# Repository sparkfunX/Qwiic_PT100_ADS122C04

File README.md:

# Qwiic PT100 ADS122C04

The Qwiic PT100 is based on the TI ADS122C04 and allows you to measure temperature accurately from
100 Ohm Platinum Resistance Thermometers using 2, 3 or 4-wire connections

[Qwiic PT100 - ADS122C04 (SPX-16770)](https://www.sparkfun.com/products/16770)

The ADS122C04 is a precision 24-bit delta-sigma analog to digital converter. It can measure voltage very
accurately through two differential or four single-ended inputs. It has a flexible input multiplexer,
a low-noise programmable gain amplifier, two programmable current sources, a voltage reference
and an in-built precision temperature sensor. In summary, it contains everything you need to measure
temperature accurately from remote sensors.

The Qwiic PT100 is dedicated to reading the temperature of 100 Ohm Platinum Resistance Thermometers
using 2, 3 or 4-wire connections. Using a 3 or 4-wire connection allows the ADS122C04 to automatically
compensate for the cable resistance. The differential input provides noise rejection for industrial
applications.

The ADS122C04 features a 2-wire I2C-compatible interface. The chip address can be changed by
reconfiguring the two jumpers A0 and A1. Please see the schematic for further details.

## Repository Contents
- **/Hardware** - Eagle schematic and PCB design files
- **/Documents** - contains the TI datasheet and application reports
- **LICENSE.md** contains the licence information

## Library

- **[Arduino Library](https://github.com/sparkfun/SparkFun_ADS122C04_ADC_Arduino_Library)** - Library to support the ADS122C04

## Probe Disconnection

If you need to test if the PT100 probe has been connected correctly to the ADS122C04, you may find [this discussion](https://forum.sparkfun.com/viewtopic.php?p=231735#p231735) useful.

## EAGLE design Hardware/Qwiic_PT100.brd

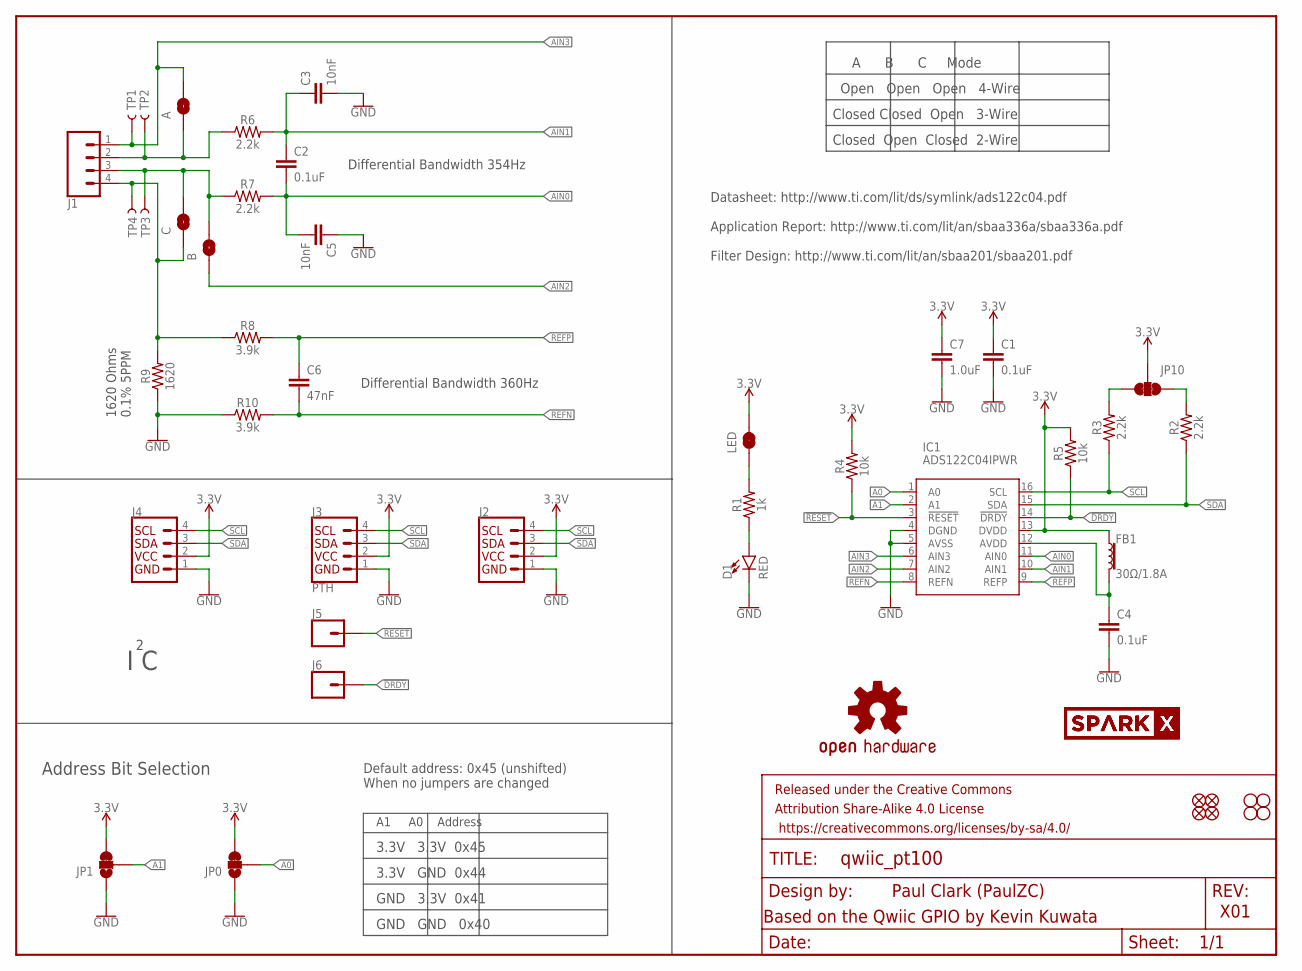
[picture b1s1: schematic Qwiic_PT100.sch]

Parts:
A: JUMPER-SMT_2_NO_SILK_ROUND; SMT-JUMPER_2_NO_SILK_ROUND
B: JUMPER-SMT_2_NO_SILK_ROUND; SMT-JUMPER_2_NO_SILK_ROUND
C: JUMPER-SMT_2_NO_SILK_ROUND; SMT-JUMPER_2_NO_SILK_ROUND
C1, C2, C4: 0.1uF; 0603
C3, C5: 10nF; 0603
C6: 47nF; 0603
C7: 1.0uF; 0603
D1: RED; LED-0603
FB1: 30Ω/1.8A; 0603
FD1, FD2: FIDUCIAL1X2; FIDUCIAL-1X2
FRAME1: FRAME-LETTER; CREATIVE_COMMONS
H1, H2: STAND-OFF
IC1: ADS122C04IPWR; SOP65P640X120-16N
J1: CONN_04LATCH; LATCHTERMINAL-5MM-4
J2, J4: QWIIC_RIGHT_ANGLE; JST04_1MM_RA
J3: PTH; 1X04_NO_SILK
J5, J6: CONN_01PTH_NO_SILK_YES_STOP; 1X01_NO_SILK
JP0, JP1: JUMPER-SMT_3_1-NC_TRACE_SILK; SMT-JUMPER_3_1-NC_TRACE_SILK
JP2, JP6: FIDUCIAL1X2; FIDUCIAL-1X2
JP3, JP4: STAND-OFF
JP10: JUMPER-SMT_3_2-NC_TRACE_SILK; SMT-JUMPER_3_2-NC_TRACE_SILK
LED: JUMPER-SMT_2_NC_TRACE_SILK; SMT-JUMPER_2_NC_TRACE_SILK
LOGO1: OSHW-LOGOMINI; OSHW-LOGO-MINI
R1: 1k; 0603
R2, R3, R6, R7: 2.2k; 0603
R4, R5: 10k; 0603
R8, R10: 3.9k; 0603
R9: 1620; 0603
TP1, TP2, TP3, TP4: TEST-POINTTP_15TH_THRU; TP_15TH
U$1, U$2: SPARKX-LOGO3; SPARKX-SMALL

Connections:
3.3V: C1.1, C7.1, FB1.1, IC1.13 (DVDD), J2.2, J3.2, J4.2, JP0.3, JP1.3, JP10.2, LED.2, R4.2, R5.2
!DRDY: IC1.14 (!DRDY), J6.1, R5.1
!RESET: IC1.3 (!RESET), J5.1, R4.1
A0: IC1.1 (A0), JP0.2
A1: IC1.2 (A1), JP1.2
AIN0: C2.2, C5.2, IC1.11 (AIN0), R7.2
AIN1: C2.1, C3.1, IC1.10 (AIN1), R6.2
AIN2: B.1, IC1.7 (AIN2)
AIN3: A.2, IC1.6 (AIN3), J1.1, TP1.P$1
GND: C1.2, C3.2, C4.2, C5.1, C7.2, D1.C, IC1.4 (DGND), IC1.5 (AVSS), J2.1, J3.1, J4.1, JP0.1, JP1.1, R9.1, R10.1
unnamed: A.1, J1.2, R6.1, TP2.P$1
unnamed: D1.A, R1.1
unnamed: LED.1, R1.2
unnamed: C4.1, FB1.2, IC1.12 (AVDD)
unnamed: B.2, C.2, J1.3, R7.1, TP3.P$1
unnamed: C.1, J1.4, R8.1, R9.2, TP4.P$1
REFN: C6.2, IC1.8 (REFN), R10.2
REFP: C6.1, IC1.9 (REFP), R8.2
SCL: IC1.16 (SCL), J2.4, J3.4, J4.4, R3.1
SCL_PU1: JP10.1, R2.2
SDA: IC1.15 (SDA), J2.3, J3.3, J4.3, R2.1
SDA_PU1: JP10.3, R3.2

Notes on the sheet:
Paul Clark (PaulZC)
X01
I C
Address Bit Selection
A1 A0 Address
3.3V 3.3V 0x45
3.3V GND 0x44
GND 3.3V 0x41
GND GND 0x40
Default address: 0x45 (unshifted) When no jumpers are changed
Based on the Qwiic GPIO by Kevin Kuwata
A B C Mode
Open Open Open 4-Wire
Closed Closed Open 3-Wire
Closed Open Closed 2-Wire
Datasheet: http://www.ti.com/lit/ds/symlink/ads122c04.pdf Application Report: http://www.ti.com/lit/an/sbaa336a/sbaa336a.pdf Filter Design: http://www.ti.com/lit/an/sbaa201/sbaa201.pdf
1620 Ohms 0.1% 5PPM
Differential Bandwidth 354Hz
Differential Bandwidth 360Hz

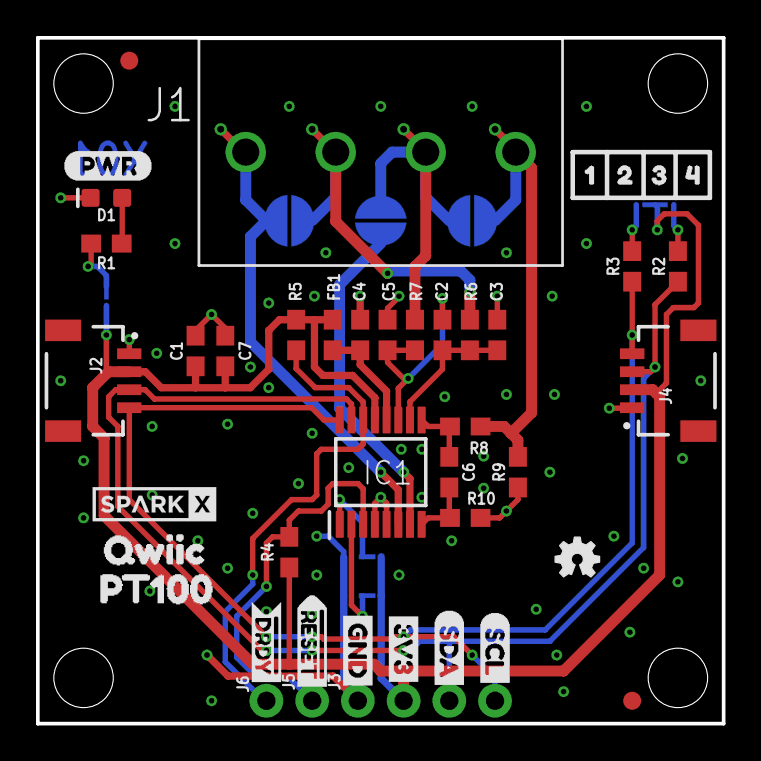
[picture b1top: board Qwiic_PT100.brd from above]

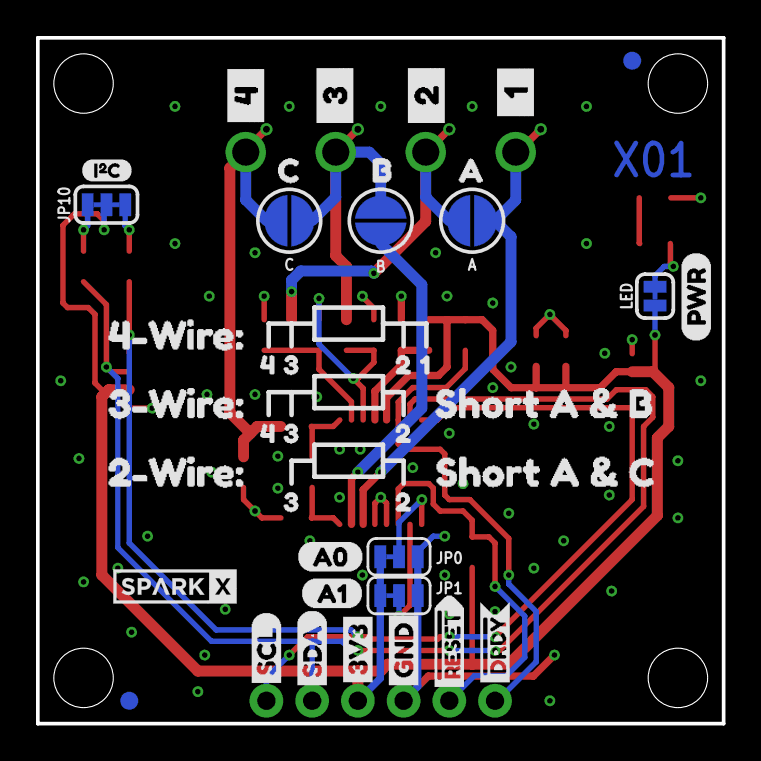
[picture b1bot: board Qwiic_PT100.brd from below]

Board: 2 copper layers, 38.1 x 38.1 mm, 93 parts (41 on the bottom side), 22 nets.

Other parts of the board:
U$3, U$26: 3V33
U$4: _1_0
U$5: A11
U$6: _2_0
U$7, U$25: GND4
U$8: PT1000
U$9: SCL6
U$10: SDA5
U$11: A00
U$12: _3_0
U$13: _4_0
U$14, U$15: #DRDY0
U$16, U$17: #RESET0
U$18: A0
U$19: B0
U$20: I_SUPER2_C-()-03
U$21, U$30, U$44: 40
U$22: C0
U$23: SCL0
U$24: SDA1
U$27, U$34, U$38, U$47: 31
U$28, U$33, U$37, U$46: 20
U$29, U$35: 15
U$31: 2#WIRE#0
U$32: QWIIC1
U$36: 3#WIRE#0
U$39, U$40: PWR0
U$41: 4#WIRE#0
U$42: SHORT_A_#_B0
U$43: SHORT_A_#_C0

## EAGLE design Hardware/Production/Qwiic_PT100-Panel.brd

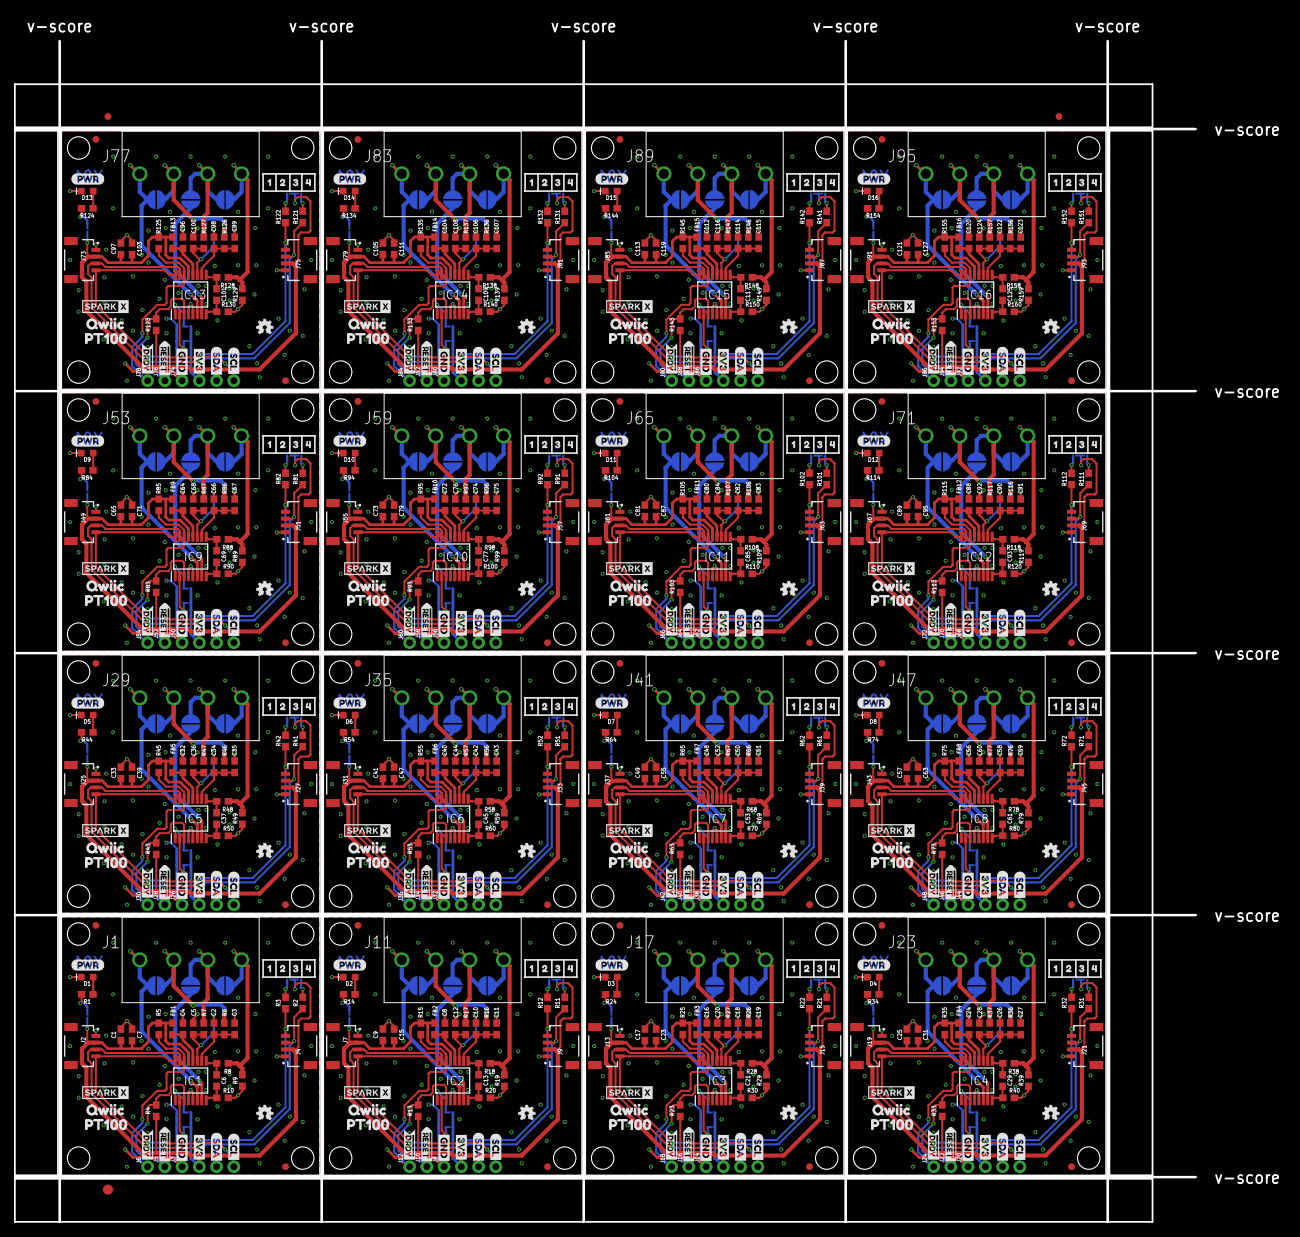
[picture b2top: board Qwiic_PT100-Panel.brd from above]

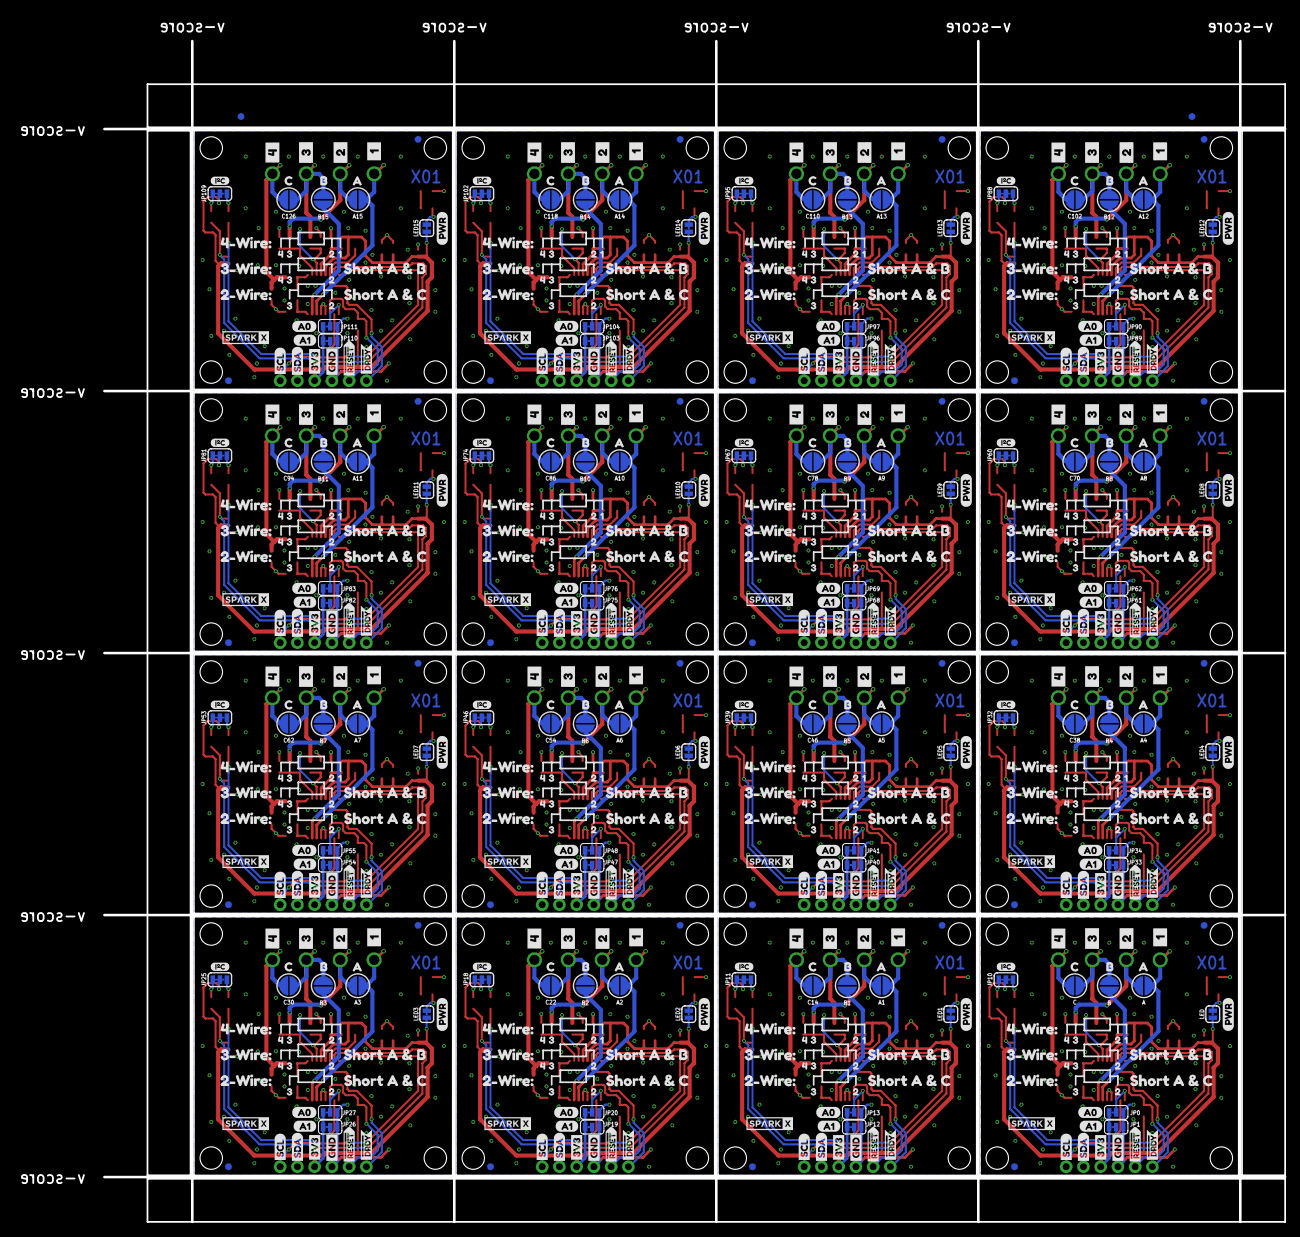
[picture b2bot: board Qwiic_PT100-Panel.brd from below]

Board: 2 copper layers, 174.0 x 174.0 mm, 1477 parts (658 on the bottom side), 352 nets.

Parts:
A, A1, A2, A3, A4, A5, A6, A7, A8, A9, A10, A11, A12, A13, A14, A15: JUMPER-SMT_2_NO_SILK_ROUND; SMT-JUMPER_2_NO_SILK_ROUND
B, B1, B2, B3, B4, B5, B6, B7, B8, B9, B10, B11, B12, B13, B14, B15: JUMPER-SMT_2_NO_SILK_ROUND; SMT-JUMPER_2_NO_SILK_ROUND
C, C14, C22, C30, C38, C46, C54, C62, C70, C78, C86, C94, C102, C110, C118, C126: JUMPER-SMT_2_NO_SILK_ROUND; SMT-JUMPER_2_NO_SILK_ROUND
C1, C2, C4, C8, C9, C10, C16, C17, C18, C24, C25, C26, C32, C33, C34, C40, C41, C42, C48, C49, C50, C56, C57, C58, C64, C65, C66, C72, C73, C74, C80, C81, C82, C88, C89, C90, C96, C97, C98, C104, C105, C106, C112, C113, C114, C120, C121, C122: 0.1uF; 0603
C3, C5, C11, C12, C19, C20, C27, C28, C35, C36, C43, C44, C51, C52, C59, C60, C67, C68, C75, C76, C83, C84, C91, C92, C99, C100, C107, C108, C115, C116, C123, C124: 10nF; 0603
C6, C13, C21, C29, C37, C45, C53, C61, C69, C77, C85, C93, C101, C109, C117, C125: 47nF; 0603
C7, C15, C23, C31, C39, C47, C55, C63, C71, C79, C87, C95, C103, C111, C119, C127: 1.0uF; 0603
D1, D2, D3, D4, D5, D6, D7, D8, D9, D10, D11, D12, D13, D14, D15, D16: RED; LED-0603
E$1, E$2, E$3, E$4: FIDUCIAL-1X2
E$5: FIDUCIAL-1.5X3
FB1, FB2, FB3, FB4, FB5, FB6, FB7, FB8, FB9, FB10, FB11, FB12, FB13, FB14, FB15, FB16: 30Ω/1.8A; 0603
FD1, FD2, FD3, FD4, FD5, FD6, FD7, FD8, FD9, FD10, FD11, FD12, FD13, FD14, FD15, FD16, FD17, FD18, FD19, FD20, FD21, FD22, FD23, FD24, FD25, FD26, FD27, FD28, FD29, FD30, FD31, FD32: FIDUCIAL1X2; FIDUCIAL-1X2
H1, H2, H3, H4, H5, H6, H7, H8, H9, H10, H11, H12, H13, H14, H15, H16, H17, H18, H19, H20, H21, H22, H23, H24, H25, H26, H27, H28, H29, H30, H31, H32: STAND-OFF
IC1, IC2, IC3, IC4, IC5, IC6, IC7, IC8, IC9, IC10, IC11, IC12, IC13, IC14, IC15, IC16: ADS122C04IPWR; SOP65P640X120-16N
J1, J11, J17, J23, J29, J35, J41, J47, J53, J59, J65, J71, J77, J83, J89, J95: LATCHTERMINAL-5MM-4
J2, J4, J7, J9, J13, J15, J19, J21, J25, J27, J31, J33, J37, J39, J43, J45, J49, J51, J55, J57, J61, J63, J67, J69, J73, J75, J79, J81, J85, J87, J91, J93: QWIIC_RIGHT_ANGLE; JST04_1MM_RA
J3, J8, J14, J20, J26, J32, J38, J44, J50, J56, J62, J68, J74, J80, J86, J92: PTH; 1X04_NO_SILK
J5, J6, J10, J12, J16, J18, J22, J24, J28, J30, J34, J36, J40, J42, J46, J48, J52, J54, J58, J60, J64, J66, J70, J72, J76, J78, J82, J84, J88, J90, J94, J96: 1X01_NO_SILK
JP0, JP1, JP12, JP13, JP19, JP20, JP26, JP27, JP33, JP34, JP40, JP41, JP47, JP48, JP54, JP55, JP61, JP62, JP68, JP69, JP75, JP76, JP82, JP83, JP89, JP90, JP96, JP97, JP103, JP104, JP110, JP111: JUMPER-SMT_3_1-NC_TRACE_SILK; SMT-JUMPER_3_1-NC_TRACE_SILK
JP2, JP6, JP8, JP9, JP16, JP17, JP23, JP24, JP30, JP31, JP37, JP38, JP44, JP45, JP51, JP52, JP58, JP59, JP65, JP66, JP72, JP73, JP79, JP80, JP86, JP87, JP93, JP94, JP100, JP101, JP107, JP108: FIDUCIAL1X2; FIDUCIAL-1X2
JP3, JP4, JP5, JP7, JP14, JP15, JP21, JP22, JP28, JP29, JP35, JP36, JP42, JP43, JP49, JP50, JP56, JP57, JP63, JP64, JP70, JP71, JP77, JP78, JP84, JP85, JP91, JP92, JP98, JP99, JP105, JP106: STAND-OFF
JP10, JP11, JP18, JP25, JP32, JP39, JP46, JP53, JP60, JP67, JP74, JP81, JP88, JP95, JP102, JP109: JUMPER-SMT_3_2-NC_TRACE_SILK; SMT-JUMPER_3_2-NC_TRACE_SILK
LED, LED1, LED2, LED3, LED4, LED5, LED6, LED7, LED8, LED9, LED10, LED11, LED12, LED13, LED14, LED15: JUMPER-SMT_2_NC_TRACE_SILK; SMT-JUMPER_2_NC_TRACE_SILK
LOGO1, LOGO2, LOGO3, LOGO4, LOGO5, LOGO6, LOGO7, LOGO8, LOGO9, LOGO10, LOGO11, LOGO12, LOGO13, LOGO14, LOGO15, LOGO16: OSHW-LOGOMINI; OSHW-LOGO-MINI
R1, R14, R24, R34, R44, R54, R64, R74, R84, R94, R104, R114, R124, R134, R144, R154: 1k; 0603
R2, R3, R6, R7, R11, R12, R16, R17, R21, R22, R26, R27, R31, R32, R36, R37, R41, R42, R46, R47, R51, R52, R56, R57, R61, R62, R66, R67, R71, R72, R76, R77, R81, R82, R86, R87, R91, R92, R96, R97, R101, R102, R106, R107, R111, R112, R116, R117, R121, R122, R126, R127, R131, R132, R136, R137, R141, R142, R146, R147, R151, R152, R156, R157: 2.2k; 0603
R4, R5, R13, R15, R23, R25, R33, R35, R43, R45, R53, R55, R63, R65, R73, R75, R83, R85, R93, R95, R103, R105, R113, R115, R123, R125, R133, R135, R143, R145, R153, R155: 10k; 0603
R8, R10, R18, R20, R28, R30, R38, R40, R48, R50, R58, R60, R68, R70, R78, R80, R88, R90, R98, R100, R108, R110, R118, R120, R128, R130, R138, R140, R148, R150, R158, R160: 3.9k; 0603
R9, R19, R29, R39, R49, R59, R69, R79, R89, R99, R109, R119, R129, R139, R149, R159: 1620; 0603
TP1, TP2, TP3, TP4, TP5, TP6, TP7, TP8, TP9, TP10, TP11, TP12, TP13, TP14, TP15, TP16, TP17, TP18, TP19, TP20, TP21, TP22, TP23, TP24, TP25, TP26, TP27, TP28, TP29, TP30, TP31, TP32, TP33, TP34, TP35, TP36, TP37, TP38, TP39, TP40, TP41, TP42, TP43, TP44, TP45, TP46, TP47, TP48, TP49, TP50, TP51, TP52, TP53, TP54, TP55, TP56, TP57, TP58, TP59, TP60, TP61, TP62, TP63, TP64: TEST-POINTTP_15TH_THRU; TP_15TH
U$1, U$2, U$45, U$48, U$93, U$94, U$139, U$140, U$185, U$186, U$231, U$232, U$277, U$278, U$323, U$324, U$369, U$370, U$415, U$416, U$461, U$462, U$507, U$508, U$553, U$554, U$599, U$600, U$645, U$646, U$691, U$692: SPARKX-LOGO3; SPARKX-SMALL
U$3, U$26, U$49, U$59, U$95, U$105, U$141, U$151, U$187, U$197, U$233, U$243, U$279, U$289, U$325, U$335, U$371, U$381, U$417, U$427, U$463, U$473, U$509, U$519, U$555, U$565, U$601, U$611, U$647, U$657, U$693, U$703: 3V33
U$4, U$66, U$112, U$158, U$204, U$250, U$296, U$342, U$388, U$434, U$480, U$526, U$572, U$618, U$664, U$710: _1_0
U$5, U$50, U$96, U$142, U$188, U$234, U$280, U$326, U$372, U$418, U$464, U$510, U$556, U$602, U$648, U$694: A11
U$6, U$67, U$113, U$159, U$205, U$251, U$297, U$343, U$389, U$435, U$481, U$527, U$573, U$619, U$665, U$711: _2_0
U$7, U$25, U$51, U$58, U$97, U$104, U$143, U$150, U$189, U$196, U$235, U$242, U$281, U$288, U$327, U$334, U$373, U$380, U$419, U$426, U$465, U$472, U$511, U$518, U$557, U$564, U$603, U$610, U$649, U$656, U$695, U$702: GND4
U$8, U$78, U$124, U$170, U$216, U$262, U$308, U$354, U$400, U$446, U$492, U$538, U$584, U$630, U$676, U$722: PT1000
U$9, U$52, U$98, U$144, U$190, U$236, U$282, U$328, U$374, U$420, U$466, U$512, U$558, U$604, U$650, U$696: SCL6
U$10, U$53, U$99, U$145, U$191, U$237, U$283, U$329, U$375, U$421, U$467, U$513, U$559, U$605, U$651, U$697: SDA5
U$11, U$54, U$100, U$146, U$192, U$238, U$284, U$330, U$376, U$422, U$468, U$514, U$560, U$606, U$652, U$698: A00
U$12, U$68, U$114, U$160, U$206, U$252, U$298, U$344, U$390, U$436, U$482, U$528, U$574, U$620, U$666, U$712: _3_0
U$13, U$69, U$115, U$161, U$207, U$253, U$299, U$345, U$391, U$437, U$483, U$529, U$575, U$621, U$667, U$713: _4_0
U$14, U$15, U$70, U$71, U$116, U$117, U$162, U$163, U$208, U$209, U$254, U$255, U$300, U$301, U$346, U$347, U$392, U$393, U$438, U$439, U$484, U$485, U$530, U$531, U$576, U$577, U$622, U$623, U$668, U$669, U$714, U$715: #DRDY0
U$16, U$17, U$72, U$73, U$118, U$119, U$164, U$165, U$210, U$211, U$256, U$257, U$302, U$303, U$348, U$349, U$394, U$395, U$440, U$441, U$486, U$487, U$532, U$533, U$578, U$579, U$624, U$625, U$670, U$671, U$716, U$717: #RESET0
U$18, U$74, U$120, U$166, U$212, U$258, U$304, U$350, U$396, U$442, U$488, U$534, U$580, U$626, U$672, U$718: A0
U$19, U$75, U$121, U$167, U$213, U$259, U$305, U$351, U$397, U$443, U$489, U$535, U$581, U$627, U$673, U$719: B0
U$20, U$55, U$101, U$147, U$193, U$239, U$285, U$331, U$377, U$423, U$469, U$515, U$561, U$607, U$653, U$699: I_SUPER2_C-()-03
U$21, U$30, U$44, U$77, U$86, U$89, U$123, U$132, U$135, U$169, U$178, U$181, U$215, U$224, U$227, U$261, U$270, U$273, U$307, U$316, U$319, U$353, U$362, U$365, U$399, U$408, U$411, U$445, U$454, U$457, U$491, U$500, U$503, U$537, U$546, U$549, U$583, U$592, U$595, U$629, U$638, U$641, U$675, U$684, U$687, U$721, U$730, U$733: 40
U$22, U$76, U$122, U$168, U$214, U$260, U$306, U$352, U$398, U$444, U$490, U$536, U$582, U$628, U$674, U$720: C0
U$23, U$56, U$102, U$148, U$194, U$240, U$286, U$332, U$378, U$424, U$470, U$516, U$562, U$608, U$654, U$700: SCL0
U$24, U$57, U$103, U$149, U$195, U$241, U$287, U$333, U$379, U$425, U$471, U$517, U$563, U$609, U$655, U$701: SDA1
U$27, U$34, U$38, U$47, U$63, U$85, U$88, U$90, U$109, U$131, U$134, U$136, U$155, U$177, U$180, U$182, U$201, U$223, U$226, U$228, U$247, U$269, U$272, U$274, U$293, U$315, U$318, U$320, U$339, U$361, U$364, U$366, U$385, U$407, U$410, U$412, U$431, U$453, U$456, U$458, U$477, U$499, U$502, U$504, U$523, U$545, U$548, U$550, U$569, U$591, U$594, U$596, U$615, U$637, U$640, U$642, U$661, U$683, U$686, U$688, U$707, U$729, U$732, U$734: 31
U$28, U$33, U$37, U$46, U$62, U$84, U$87, U$91, U$108, U$130, U$133, U$137, U$154, U$176, U$179, U$183, U$200, U$222, U$225, U$229, U$246, U$268, U$271, U$275, U$292, U$314, U$317, U$321, U$338, U$360, U$363, U$367, U$384, U$406, U$409, U$413, U$430, U$452, U$455, U$459, U$476, U$498, U$501, U$505, U$522, U$544, U$547, U$551, U$568, U$590, U$593, U$597, U$614, U$636, U$639, U$643, U$660, U$682, U$685, U$689, U$706, U$728, U$731, U$735: 20
U$29, U$35, U$61, U$92, U$107, U$138, U$153, U$184, U$199, U$230, U$245, U$276, U$291, U$322, U$337, U$368, U$383, U$414, U$429, U$460, U$475, U$506, U$521, U$552, U$567, U$598, U$613, U$644, U$659, U$690, U$705, U$736: 15
U$31, U$79, U$125, U$171, U$217, U$263, U$309, U$355, U$401, U$447, U$493, U$539, U$585, U$631, U$677, U$723: 2#WIRE#0
U$32, U$60, U$106, U$152, U$198, U$244, U$290, U$336, U$382, U$428, U$474, U$520, U$566, U$612, U$658, U$704: QWIIC1
U$36, U$80, U$126, U$172, U$218, U$264, U$310, U$356, U$402, U$448, U$494, U$540, U$586, U$632, U$678, U$724: 3#WIRE#0
U$39, U$40, U$64, U$65, U$110, U$111, U$156, U$157, U$202, U$203, U$248, U$249, U$294, U$295, U$340, U$341, U$386, U$387, U$432, U$433, U$478, U$479, U$524, U$525, U$570, U$571, U$616, U$617, U$662, U$663, U$708, U$709: PWR0
U$41, U$81, U$127, U$173, U$219, U$265, U$311, U$357, U$403, U$449, U$495, U$541, U$587, U$633, U$679, U$725: 4#WIRE#0
U$42, U$82, U$128, U$174, U$220, U$266, U$312, U$358, U$404, U$450, U$496, U$542, U$588, U$634, U$680, U$726: SHORT_A_#_B0
U$43, U$83, U$129, U$175, U$221, U$267, U$313, U$359, U$405, U$451, U$497, U$543, U$589, U$635, U$681, U$727: SHORT_A_#_C0

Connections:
3.3V: C1.1, C7.1, FB1.1, IC1.13, J2.2, J3.2, J4.2, JP0.3, JP1.3, JP10.2, LED.2, R4.2, R5.2
3.3V1: C9.1, C15.1, FB2.1, IC2.13, J7.2, J8.2, J9.2, JP11.2, JP12.3, JP13.3, LED1.2, R13.2, R15.2
3.3V2: C17.1, C23.1, FB3.1, IC3.13, J13.2, J14.2, J15.2, JP18.2, JP19.3, JP20.3, LED2.2, R23.2, R25.2
3.3V3: C25.1, C31.1, FB4.1, IC4.13, J19.2, J20.2, J21.2, JP25.2, JP26.3, JP27.3, LED3.2, R33.2, R35.2
3.3V4: C33.1, C39.1, FB5.1, IC5.13, J25.2, J26.2, J27.2, JP32.2, JP33.3, JP34.3, LED4.2, R43.2, R45.2
3.3V5: C41.1, C47.1, FB6.1, IC6.13, J31.2, J32.2, J33.2, JP39.2, JP40.3, JP41.3, LED5.2, R53.2, R55.2
3.3V6: C49.1, C55.1, FB7.1, IC7.13, J37.2, J38.2, J39.2, JP46.2, JP47.3, JP48.3, LED6.2, R63.2, R65.2
3.3V7: C57.1, C63.1, FB8.1, IC8.13, J43.2, J44.2, J45.2, JP53.2, JP54.3, JP55.3, LED7.2, R73.2, R75.2
3.3V8: C65.1, C71.1, FB9.1, IC9.13, J49.2, J50.2, J51.2, JP60.2, JP61.3, JP62.3, LED8.2, R83.2, R85.2
3.3V9: C73.1, C79.1, FB10.1, IC10.13, J55.2, J56.2, J57.2, JP67.2, JP68.3, JP69.3, LED9.2, R93.2, R95.2
3.3V10: C81.1, C87.1, FB11.1, IC11.13, J61.2, J62.2, J63.2, JP74.2, JP75.3, JP76.3, LED10.2, R103.2, R105.2
3.3V11: C89.1, C95.1, FB12.1, IC12.13, J67.2, J68.2, J69.2, JP81.2, JP82.3, JP83.3, LED11.2, R113.2, R115.2
3.3V12: C97.1, C103.1, FB13.1, IC13.13, J73.2, J74.2, J75.2, JP88.2, JP89.3, JP90.3, LED12.2, R123.2, R125.2
3.3V13: C105.1, C111.1, FB14.1, IC14.13, J79.2, J80.2, J81.2, JP95.2, JP96.3, JP97.3, LED13.2, R133.2, R135.2
3.3V14: C113.1, C119.1, FB15.1, IC15.13, J85.2, J86.2, J87.2, JP102.2, JP103.3, JP104.3, LED14.2, R143.2, R145.2
3.3V15: C121.1, C127.1, FB16.1, IC16.13, J91.2, J92.2, J93.2, JP109.2, JP110.3, JP111.3, LED15.2, R153.2, R155.2
!DRDY: IC1.14, J6.1, R5.1
!DRDY1: IC2.14, J12.1, R15.1
!DRDY2: IC3.14, J18.1, R25.1
!DRDY3: IC4.14, J24.1, R35.1
!DRDY4: IC5.14, J30.1, R45.1
!DRDY5: IC6.14, J36.1, R55.1
!DRDY6: IC7.14, J42.1, R65.1
!DRDY7: IC8.14, J48.1, R75.1
!DRDY8: IC9.14, J54.1, R85.1
!DRDY9: IC10.14, J60.1, R95.1
!DRDY10: IC11.14, J66.1, R105.1
!DRDY11: IC12.14, J72.1, R115.1
!DRDY12: IC13.14, J78.1, R125.1
!DRDY13: IC14.14, J84.1, R135.1
!DRDY14: IC15.14, J90.1, R145.1
!DRDY15: IC16.14, J96.1, R155.1
!RESET: IC1.3, J5.1, R4.1
!RESET1: IC2.3, J10.1, R13.1
!RESET2: IC3.3, J16.1, R23.1
!RESET3: IC4.3, J22.1, R33.1
!RESET4: IC5.3, J28.1, R43.1
!RESET5: IC6.3, J34.1, R53.1
!RESET6: IC7.3, J40.1, R63.1
!RESET7: IC8.3, J46.1, R73.1
!RESET8: IC9.3, J52.1, R83.1
!RESET9: IC10.3, J58.1, R93.1
!RESET10: IC11.3, J64.1, R103.1
!RESET11: IC12.3, J70.1, R113.1
!RESET12: IC13.3, J76.1, R123.1
!RESET13: IC14.3, J82.1, R133.1
!RESET14: IC15.3, J88.1, R143.1
!RESET15: IC16.3, J94.1, R153.1
A0: IC1.1, JP0.2
A1: IC1.2, JP1.2
A2: IC2.1, JP13.2
A3: IC2.2, JP12.2
A4: IC3.1, JP20.2
A5: IC3.2, JP19.2
A6: IC4.1, JP27.2
A7: IC4.2, JP26.2
A8: IC5.1, JP34.2
A9: IC5.2, JP33.2
A10: IC6.1, JP41.2
A11: IC6.2, JP40.2
A12: IC7.1, JP48.2
A13: IC7.2, JP47.2
A14: IC8.1, JP55.2
A15: IC8.2, JP54.2
A16: IC9.1, JP62.2
A17: IC9.2, JP61.2
A18: IC10.1, JP69.2
A19: IC10.2, JP68.2
A20: IC11.1, JP76.2
A21: IC11.2, JP75.2
A22: IC12.1, JP83.2
A23: IC12.2, JP82.2
A24: IC13.1, JP90.2
A25: IC13.2, JP89.2
A26: IC14.1, JP97.2
A27: IC14.2, JP96.2
A28: IC15.1, JP104.2
A29: IC15.2, JP103.2
A30: IC16.1, JP111.2
A31: IC16.2, JP110.2
AIN0: C2.2, C5.2, IC1.11, R7.2
AIN1: C2.1, C3.1, IC1.10, R6.2
AIN2: B.1, IC1.7
AIN3: A.2, IC1.6, J1.1, TP1.P$1
AIN4: C10.1, C11.1, IC2.10, R16.2
AIN5: A1.2, IC2.6, J11.1, TP5.P$1
AIN6: B1.1, IC2.7
AIN7: C10.2, C12.2, IC2.11, R17.2
AIN8: C18.1, C19.1, IC3.10, R26.2
AIN9: A2.2, IC3.6, J17.1, TP9.P$1
AIN10: B2.1, IC3.7
AIN11: C18.2, C20.2, IC3.11, R27.2
AIN12: C26.1, C27.1, IC4.10, R36.2
AIN13: A3.2, IC4.6, J23.1, TP13.P$1
AIN14: B3.1, IC4.7
AIN15: C26.2, C28.2, IC4.11, R37.2
AIN16: C34.1, C35.1, IC5.10, R46.2
AIN17: A4.2, IC5.6, J29.1, TP17.P$1
AIN18: B4.1, IC5.7
AIN19: C34.2, C36.2, IC5.11, R47.2
AIN20: C42.1, C43.1, IC6.10, R56.2
AIN21: A5.2, IC6.6, J35.1, TP21.P$1
AIN22: B5.1, IC6.7
AIN23: C42.2, C44.2, IC6.11, R57.2
AIN24: C50.1, C51.1, IC7.10, R66.2
AIN25: A6.2, IC7.6, J41.1, TP25.P$1
AIN26: B6.1, IC7.7
AIN27: C50.2, C52.2, IC7.11, R67.2
AIN28: C58.1, C59.1, IC8.10, R76.2
AIN29: A7.2, IC8.6, J47.1, TP29.P$1
AIN30: B7.1, IC8.7
AIN31: C58.2, C60.2, IC8.11, R77.2
AIN32: C66.1, C67.1, IC9.10, R86.2
AIN33: A8.2, IC9.6, J53.1, TP33.P$1
AIN34: B8.1, IC9.7
AIN35: C66.2, C68.2, IC9.11, R87.2
AIN36: C74.1, C75.1, IC10.10, R96.2
AIN37: A9.2, IC10.6, J59.1, TP37.P$1
AIN38: B9.1, IC10.7
AIN39: C74.2, C76.2, IC10.11, R97.2
AIN40: C82.1, C83.1, IC11.10, R106.2
AIN41: A10.2, IC11.6, J65.1, TP41.P$1
AIN42: B10.1, IC11.7
AIN43: C82.2, C84.2, IC11.11, R107.2
AIN44: C90.1, C91.1, IC12.10, R116.2
AIN45: A11.2, IC12.6, J71.1, TP45.P$1
AIN46: B11.1, IC12.7
AIN47: C90.2, C92.2, IC12.11, R117.2
AIN48: C98.1, C99.1, IC13.10, R126.2
AIN49: A12.2, IC13.6, J77.1, TP49.P$1
AIN50: B12.1, IC13.7
AIN51: C98.2, C100.2, IC13.11, R127.2
AIN52: C106.1, C107.1, IC14.10, R136.2
AIN53: A13.2, IC14.6, J83.1, TP53.P$1
AIN54: B13.1, IC14.7
AIN55: C106.2, C108.2, IC14.11, R137.2
AIN56: C114.1, C115.1, IC15.10, R146.2
AIN57: A14.2, IC15.6, J89.1, TP57.P$1
AIN58: B14.1, IC15.7
AIN59: C114.2, C116.2, IC15.11, R147.2
AIN60: C122.1, C123.1, IC16.10, R156.2
AIN61: A15.2, IC16.6, J95.1, TP61.P$1
AIN62: B15.1, IC16.7
AIN63: C122.2, C124.2, IC16.11, R157.2
GND: C1.2, C3.2, C4.2, C5.1, C7.2, D1.C, IC1.4, IC1.5, J2.1, J3.1, J4.1, JP0.1, JP1.1, R9.1, R10.1
GND1: C8.2, C9.2, C11.2, C12.1, C15.2, D2.C, IC2.4, IC2.5, J7.1, J8.1, J9.1, JP12.1, JP13.1, R19.1, R20.1
GND2: C16.2, C17.2, C19.2, C20.1, C23.2, D3.C, IC3.4, IC3.5, J13.1, J14.1, J15.1, JP19.1, JP20.1, R29.1, R30.1
GND3: C24.2, C25.2, C27.2, C28.1, C31.2, D4.C, IC4.4, IC4.5, J19.1, J20.1, J21.1, JP26.1, JP27.1, R39.1, R40.1
GND4: C32.2, C33.2, C35.2, C36.1, C39.2, D5.C, IC5.4, IC5.5, J25.1, J26.1, J27.1, JP33.1, JP34.1, R49.1, R50.1
GND5: C40.2, C41.2, C43.2, C44.1, C47.2, D6.C, IC6.4, IC6.5, J31.1, J32.1, J33.1, JP40.1, JP41.1, R59.1, R60.1
GND6: C48.2, C49.2, C51.2, C52.1, C55.2, D7.C, IC7.4, IC7.5, J37.1, J38.1, J39.1, JP47.1, JP48.1, R69.1, R70.1
GND7: C56.2, C57.2, C59.2, C60.1, C63.2, D8.C, IC8.4, IC8.5, J43.1, J44.1, J45.1, JP54.1, JP55.1, R79.1, R80.1
GND8: C64.2, C65.2, C67.2, C68.1, C71.2, D9.C, IC9.4, IC9.5, J49.1, J50.1, J51.1, JP61.1, JP62.1, R89.1, R90.1
GND9: C72.2, C73.2, C75.2, C76.1, C79.2, D10.C, IC10.4, IC10.5, J55.1, J56.1, J57.1, JP68.1, JP69.1, R99.1, R100.1
GND10: C80.2, C81.2, C83.2, C84.1, C87.2, D11.C, IC11.4, IC11.5, J61.1, J62.1, J63.1, JP75.1, JP76.1, R109.1, R110.1
GND11: C88.2, C89.2, C91.2, C92.1, C95.2, D12.C, IC12.4, IC12.5, J67.1, J68.1, J69.1, JP82.1, JP83.1, R119.1, R120.1
GND12: C96.2, C97.2, C99.2, C100.1, C103.2, D13.C, IC13.4, IC13.5, J73.1, J74.1, J75.1, JP89.1, JP90.1, R129.1, R130.1
GND13: C104.2, C105.2, C107.2, C108.1, C111.2, D14.C, IC14.4, IC14.5, J79.1, J80.1, J81.1, JP96.1, JP97.1, R139.1, R140.1
GND14: C112.2, C113.2, C115.2, C116.1, C119.2, D15.C, IC15.4, IC15.5, J85.1, J86.1, J87.1, JP103.1, JP104.1, R149.1, R150.1
GND15: C120.2, C121.2, C123.2, C124.1, C127.2, D16.C, IC16.4, IC16.5, J91.1, J92.1, J93.1, JP110.1, JP111.1, R159.1, R160.1
unnamed: A.1, J1.2, R6.1, TP2.P$1
unnamed: D1.A, R1.1
unnamed: LED.1, R1.2
unnamed: C4.1, FB1.2, IC1.12
unnamed: B.2, C.2, J1.3, R7.1, TP3.P$1
unnamed: C.1, J1.4, R8.1, R9.2, TP4.P$1
unnamed: D2.A, R14.1
unnamed: LED1.1, R14.2
unnamed: C8.1, FB2.2, IC2.12
unnamed: A1.1, J11.2, R16.1, TP6.P$1
unnamed: B1.2, C14.2, J11.3, R17.1, TP7.P$1
unnamed: C14.1, J11.4, R18.1, R19.2, TP8.P$1
unnamed: D3.A, R24.1
unnamed: LED2.1, R24.2
unnamed: C16.1, FB3.2, IC3.12
unnamed: A2.1, J17.2, R26.1, TP10.P$1
unnamed: B2.2, C22.2, J17.3, R27.1, TP11.P$1
unnamed: C22.1, J17.4, R28.1, R29.2, TP12.P$1
unnamed: D4.A, R34.1
unnamed: LED3.1, R34.2
unnamed: C24.1, FB4.2, IC4.12
unnamed: A3.1, J23.2, R36.1, TP14.P$1
unnamed: B3.2, C30.2, J23.3, R37.1, TP15.P$1
unnamed: C30.1, J23.4, R38.1, R39.2, TP16.P$1
unnamed: D5.A, R44.1
unnamed: LED4.1, R44.2
unnamed: C32.1, FB5.2, IC5.12
unnamed: A4.1, J29.2, R46.1, TP18.P$1
unnamed: B4.2, C38.2, J29.3, R47.1, TP19.P$1
unnamed: C38.1, J29.4, R48.1, R49.2, TP20.P$1
unnamed: D6.A, R54.1
unnamed: LED5.1, R54.2
unnamed: C40.1, FB6.2, IC6.12
unnamed: A5.1, J35.2, R56.1, TP22.P$1
unnamed: B5.2, C46.2, J35.3, R57.1, TP23.P$1
unnamed: C46.1, J35.4, R58.1, R59.2, TP24.P$1
unnamed: D7.A, R64.1
unnamed: LED6.1, R64.2
unnamed: C48.1, FB7.2, IC7.12
unnamed: A6.1, J41.2, R66.1, TP26.P$1
unnamed: B6.2, C54.2, J41.3, R67.1, TP27.P$1
unnamed: C54.1, J41.4, R68.1, R69.2, TP28.P$1
unnamed: D8.A, R74.1
unnamed: LED7.1, R74.2
unnamed: C56.1, FB8.2, IC8.12
unnamed: A7.1, J47.2, R76.1, TP30.P$1
unnamed: B7.2, C62.2, J47.3, R77.1, TP31.P$1
unnamed: C62.1, J47.4, R78.1, R79.2, TP32.P$1
unnamed: D9.A, R84.1
unnamed: LED8.1, R84.2
unnamed: C64.1, FB9.2, IC9.12
unnamed: A8.1, J53.2, R86.1, TP34.P$1
unnamed: B8.2, C70.2, J53.3, R87.1, TP35.P$1
unnamed: C70.1, J53.4, R88.1, R89.2, TP36.P$1
unnamed: D10.A, R94.1
unnamed: LED9.1, R94.2
unnamed: C72.1, FB10.2, IC10.12
unnamed: A9.1, J59.2, R96.1, TP38.P$1
unnamed: B9.2, C78.2, J59.3, R97.1, TP39.P$1
unnamed: C78.1, J59.4, R98.1, R99.2, TP40.P$1
unnamed: D11.A, R104.1
unnamed: LED10.1, R104.2
unnamed: C80.1, FB11.2, IC11.12
unnamed: A10.1, J65.2, R106.1, TP42.P$1
unnamed: B10.2, C86.2, J65.3, R107.1, TP43.P$1
unnamed: C86.1, J65.4, R108.1, R109.2, TP44.P$1
unnamed: D12.A, R114.1
unnamed: LED11.1, R114.2
unnamed: C88.1, FB12.2, IC12.12
unnamed: A11.1, J71.2, R116.1, TP46.P$1
unnamed: B11.2, C94.2, J71.3, R117.1, TP47.P$1
unnamed: C94.1, J71.4, R118.1, R119.2, TP48.P$1
unnamed: D13.A, R124.1
unnamed: LED12.1, R124.2
unnamed: C96.1, FB13.2, IC13.12
unnamed: A12.1, J77.2, R126.1, TP50.P$1
unnamed: B12.2, C102.2, J77.3, R127.1, TP51.P$1
unnamed: C102.1, J77.4, R128.1, R129.2, TP52.P$1
unnamed: D14.A, R134.1
unnamed: LED13.1, R134.2
unnamed: C104.1, FB14.2, IC14.12
unnamed: A13.1, J83.2, R136.1, TP54.P$1
unnamed: B13.2, C110.2, J83.3, R137.1, TP55.P$1
unnamed: C110.1, J83.4, R138.1, R139.2, TP56.P$1
unnamed: D15.A, R144.1
unnamed: LED14.1, R144.2
unnamed: C112.1, FB15.2, IC15.12
unnamed: A14.1, J89.2, R146.1, TP58.P$1
unnamed: B14.2, C118.2, J89.3, R147.1, TP59.P$1
unnamed: C118.1, J89.4, R148.1, R149.2, TP60.P$1
unnamed: D16.A, R154.1
unnamed: LED15.1, R154.2
unnamed: C120.1, FB16.2, IC16.12
unnamed: A15.1, J95.2, R156.1, TP62.P$1
unnamed: B15.2, C126.2, J95.3, R157.1, TP63.P$1
unnamed: C126.1, J95.4, R158.1, R159.2, TP64.P$1
REFN: C6.2, IC1.8, R10.2
REFN1: C13.2, IC2.8, R20.2
REFN2: C21.2, IC3.8, R30.2
REFN3: C29.2, IC4.8, R40.2
REFN4: C37.2, IC5.8, R50.2
REFN5: C45.2, IC6.8, R60.2
REFN6: C53.2, IC7.8, R70.2
REFN7: C61.2, IC8.8, R80.2
REFN8: C69.2, IC9.8, R90.2
REFN9: C77.2, IC10.8, R100.2
REFN10: C85.2, IC11.8, R110.2
REFN11: C93.2, IC12.8, R120.2
REFN12: C101.2, IC13.8, R130.2
REFN13: C109.2, IC14.8, R140.2
REFN14: C117.2, IC15.8, R150.2
REFN15: C125.2, IC16.8, R160.2
REFP: C6.1, IC1.9, R8.2
REFP1: C13.1, IC2.9, R18.2
REFP2: C21.1, IC3.9, R28.2
REFP3: C29.1, IC4.9, R38.2
REFP4: C37.1, IC5.9, R48.2
REFP5: C45.1, IC6.9, R58.2
REFP6: C53.1, IC7.9, R68.2
REFP7: C61.1, IC8.9, R78.2
REFP8: C69.1, IC9.9, R88.2
REFP9: C77.1, IC10.9, R98.2
REFP10: C85.1, IC11.9, R108.2
REFP11: C93.1, IC12.9, R118.2
REFP12: C101.1, IC13.9, R128.2
REFP13: C109.1, IC14.9, R138.2
REFP14: C117.1, IC15.9, R148.2
REFP15: C125.1, IC16.9, R158.2
SCL: IC1.16, J2.4, J3.4, J4.4, R3.1
SCL1: IC2.16, J7.4, J8.4, J9.4, R12.1
SCL2: IC3.16, J13.4, J14.4, J15.4, R22.1
SCL3: IC4.16, J19.4, J20.4, J21.4, R32.1
SCL4: IC5.16, J25.4, J26.4, J27.4, R42.1
SCL5: IC6.16, J31.4, J32.4, J33.4, R52.1
SCL6: IC7.16, J37.4, J38.4, J39.4, R62.1
SCL7: IC8.16, J43.4, J44.4, J45.4, R72.1
SCL8: IC9.16, J49.4, J50.4, J51.4, R82.1
SCL9: IC10.16, J55.4, J56.4, J57.4, R92.1
SCL10: IC11.16, J61.4, J62.4, J63.4, R102.1
SCL11: IC12.16, J67.4, J68.4, J69.4, R112.1
SCL12: IC13.16, J73.4, J74.4, J75.4, R122.1
SCL13: IC14.16, J79.4, J80.4, J81.4, R132.1
SCL14: IC15.16, J85.4, J86.4, J87.4, R142.1
SCL15: IC16.16, J91.4, J92.4, J93.4, R152.1
SCL_PU1: JP10.1, R2.2
SCL_PU2: JP11.1, R11.2
SCL_PU3: JP18.1, R21.2
SCL_PU4: JP25.1, R31.2
SCL_PU5: JP32.1, R41.2
SCL_PU6: JP39.1, R51.2
SCL_PU7: JP46.1, R61.2
SCL_PU8: JP53.1, R71.2
SCL_PU9: JP60.1, R81.2
SCL_PU10: JP67.1, R91.2
SCL_PU11: JP74.1, R101.2
SCL_PU12: JP81.1, R111.2
SCL_PU13: JP88.1, R121.2
SCL_PU14: JP95.1, R131.2
SCL_PU15: JP102.1, R141.2
SCL_PU16: JP109.1, R151.2
SDA: IC1.15, J2.3, J3.3, J4.3, R2.1
SDA1: IC2.15, J7.3, J8.3, J9.3, R11.1
SDA2: IC3.15, J13.3, J14.3, J15.3, R21.1
SDA3: IC4.15, J19.3, J20.3, J21.3, R31.1
SDA4: IC5.15, J25.3, J26.3, J27.3, R41.1
SDA5: IC6.15, J31.3, J32.3, J33.3, R51.1
SDA6: IC7.15, J37.3, J38.3, J39.3, R61.1
SDA7: IC8.15, J43.3, J44.3, J45.3, R71.1
SDA8: IC9.15, J49.3, J50.3, J51.3, R81.1
SDA9: IC10.15, J55.3, J56.3, J57.3, R91.1
SDA10: IC11.15, J61.3, J62.3, J63.3, R101.1
SDA11: IC12.15, J67.3, J68.3, J69.3, R111.1
SDA12: IC13.15, J73.3, J74.3, J75.3, R121.1
SDA13: IC14.15, J79.3, J80.3, J81.3, R131.1
SDA14: IC15.15, J85.3, J86.3, J87.3, R141.1
SDA15: IC16.15, J91.3, J92.3, J93.3, R151.1
SDA_PU1: JP10.3, R3.2
SDA_PU2: JP11.3, R12.2
SDA_PU3: JP18.3, R22.2
SDA_PU4: JP25.3, R32.2
SDA_PU5: JP32.3, R42.2
SDA_PU6: JP39.3, R52.2
SDA_PU7: JP46.3, R62.2
SDA_PU8: JP53.3, R72.2
SDA_PU9: JP60.3, R82.2
SDA_PU10: JP67.3, R92.2
SDA_PU11: JP74.3, R102.2
SDA_PU12: JP81.3, R112.2
SDA_PU13: JP88.3, R122.2
SDA_PU14: JP95.3, R132.2
SDA_PU15: JP102.3, R142.2
SDA_PU16: JP109.3, R152.2

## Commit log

2020-05-13 Copying across PaulZC/Qwiic_PT100
2020-06-26 Update README.md
    This repo will be moving over to SparkFunX soon!
2021-03-22 Remove New-Parts

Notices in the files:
parts and their libraries:
SparkFun-Resistors: Licensing: Creative Commons ShareAlike 4.0 International - https://creativecommons.org/licenses/by-sa/4.0
SparkFun-Aesthetics: Released under the Creative Commons Attribution Share-Alike 4.0 License
SparkFun-Aesthetics: https://creativecommons.org/licenses/by-sa/4.0
